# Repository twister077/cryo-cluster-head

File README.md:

# CryoClusterHead — Open-Source Cluster Headache Detection & Relief System

> **⚠ Experimental Research Project.** Not a certified medical product. Use at your own risk.

## Overview

Cluster headaches are among the most excruciatingly painful conditions known. This project explores an open-source hardware and software approach to **early detection of cluster headache flare-ups** using continuous skin temperature monitoring. 

By tracking rapid localized temperature changes ($\Delta T/\Delta t$) at the temple/neck area during the prodromal phase, our goal is to provide an early warning notification **minutes before peak pain hits**, allowing for timely intervention (such as cold therapy or medication).

---

## Current Focus & Development Tracks

The repository is structured into two main tracks:

### 🚀 Track A — Non-BLE Test Patch (Active Focus)
- **Hardware:** Miniature round PCB (`cryo-alert-patch/hardware/pcb/`) featuring **STM32L011** MCU + **TMP117** high-precision temperature sensor (B.Cu contact), CR1220 battery, piezo buzzer, LED, and tactile switch (`SW1`).
- **Firmware (`cryo-alert-patch/firmware-stm32/`)**: PlatformIO / STM32Cube HAL implementation featuring TMP117 I2C driver, ADC battery monitoring, alert state machine, and robust **$\Delta T/\Delta t$ flare-up detection** (validated with a host-side unit test suite).

### 📡 Track B — BLE & Companion Ecosystem (Planned / Later)
- **Hardware & Software:** nRF52832-based variants, `cryo-active-cooler/`, and `cryo-mobile-app/` (Flutter + Rust core).
- **Status:** Documented for future integration after Track A hardware testing and validation are completed.

---

## Community & Collaboration Welcome!

Building open-source medical/health hardware and embedded firmware is a massive undertaking for a single developer. **I cannot do this alone!** 

Whether you are an embedded firmware engineer, PCB designer (KiCad), mobile app developer, or a fellow cluster headache sufferer / researcher wanting to share insights — **your input, contributions, and feedback are immensely welcome.**

- **Open Issues & PRs:** Feel free to open issues or submit pull requests directly in this repository.
- **Discussions / Contact:** Reach out via GitHub issues or discussions to collaborate.

---

## Repository Structure

- `cryo-alert-patch/` — Hardware schematics, Gerber files, and firmware (`firmware-stm32/` for STM32 test track, `firmware-zephyr-ble/` for Zephyr/BLE).
- `cryo-mobile-app/` — Flutter companion app with Rust core for real-time $\Delta T/\Delta t$ analysis *(Track B)*.
- `cryo-active-cooler/` — Optional Peltier active cooling module concept *(Track B)*.
- `plan.md` — Detailed multi-phase project roadmap.

## License

- **Firmware:** MIT
- **Hardware:** CERN-OHL-S-2.0

---

## Contributors & AI Co-Developer

- **Twister077** — Project Initiator, Lead Concept & Hardware Architect.
- **Hermes Agent (Nous Research)** — AI Co-Developer & Engineering Assistant (assisted with KiCad schematic reconstruction, DRC/ERC validation, Gerber preparation, and STM32 PlatformIO firmware/testing).

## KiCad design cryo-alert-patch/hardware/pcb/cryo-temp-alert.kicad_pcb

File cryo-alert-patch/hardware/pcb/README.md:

# Cryo Temp Alert PCB — v6

**Date:** 2026-09-08
**Status:** Production-ready (0 real DRC errors, 32 cosmetic warnings; ERC 0 errors)
**Validation:** KiCad DRC/ERC + MCP SVG render + netlist cross-check

## Specs
- Board: Ø34mm round (radius 17mm)
- Layers: 2 (F.Cu + B.Cu)
- Components: 13 footprints
  - **U1** STM32L011 MCU (TSSOP-20) — F.Cu at (-3, 0)
  - **U2** TMP117 temperature sensor (TMP117xxDRV, WSON-6-1EP) — **B.Cu** at (0, 7) ← skin contact
  - **BT1** CR1220 battery holder — F.Cu
  - **BZ1** Piezo buzzer — F.Cu
  - **LED1** SMD LED — F.Cu
  - **SW1** SKQG tactile switch — F.Cu
  - **J1** Pin header 1x4 (POGO programmer) — F.Cu
  - **R1, R2** 4.7k I2C pull-ups — F.Cu
  - **R3** 10k (NRST pull-up), **R4** LED current limiter — F.Cu
  - **C1, C2** 100nF decoupling — B.Cu near MCU
- Nets: 12 (GND, VCC, SDA, SCL, NRST, VBAT_SENSE, BUZZER, LED_SIG, SW_SIG, I2C_ADDR, VDDA, DEC_100NF)

## Temperature sensor: TMP117 (deliberate choice)
The board uses the **TMP117** (by TI) as the skin temperature sensor, deliberately instead of the
MAX30208 — among other reasons, because of the simpler wiring in this phase.

- **Schematic symbol:** `Sensor_Temperature:TMP117xxDRV` (value `TMP117xxDRV`)
- **PCB footprint:** `WSON-6-1EP_2x2mm_P0.65mm_EP1x1.6mm` on B.Cu
- Same I2C pinout as the MAX30208 (SCL/SDA/ADD0/ALERT/V+/GND), so it can later be
  swapped for the MAX30208 in the Bluetooth revision.

> **Future:** the next revision will get Bluetooth (nRF) and the MAX30208 sensor.
> For now both the schematic and PCB are configured for the TMP117.

## Schematic (rebuilt 2026-09-08)
The schematic was fully rebuilt so it renders correctly in the KiCad GUI:
- **Real root UUID** (was all-null `00000000-...` → blank GUI sheet)
- **Real net labels** (46 total) connect the pins electrically
- **ERC: 0 errors** (7 cosmetic warnings: spare GPIOs on power rails + VBAT_SENSE test point)
- Components on an A4 sheet with net labels instead of only physical wires

## Contents of this bundle (v6)
- `cryo-temp-alert.kicad_sch` — schematic (rebuilt, renders correctly)
- `cryo-temp-alert.kicad_pcb` — PCB (U2 = TMP117)
- `cryo-temp-alert.kicad_pro` — project file
- `cryo-temp-alert.kicad_prl` — layout
- `sym-lib-table` / `fp-lib-table` — library configuration
- `schematic.pdf` — schematic export (rebuilt)
- `gerbers/cryo-temp-alert-jlcpcb.zip` — JLCPCB fabrication bundle (fresh export)
- `renders/cryo-3d-renders.zip` — 3D renders
- `cryo-temp-alert-drc.rpt` — KiCad DRC report (32 cosmetic warnings, 0 errors)
- `README.md` — this file

## For JLCPCB fabrication
Upload `gerbers/cryo-temp-alert-jlcpcb.zip` to https://jlcpcb.com/quote.
Contains 7 Gerber layers + drill + job file.

## For manual assembly
1. **U2 (TMP117)** on the **bottom** (B.Cu, skin-contact side)
2. Remaining components on top (F.Cu)
3. Insert CR1220 battery into BT1
4. Program via J1 POGO pads (SWDIO/SWDCLK/RESET/GND)

## Layers / design notes
- Sensor on B.Cu for skin-temperature measurement
- Pad-to-mask clearance 0.05mm (0.65mm pitch)
- Minimum track width 0.2mm

Validated: 0 real DRC errors, 0 ERC errors, 0 unconnected pads.

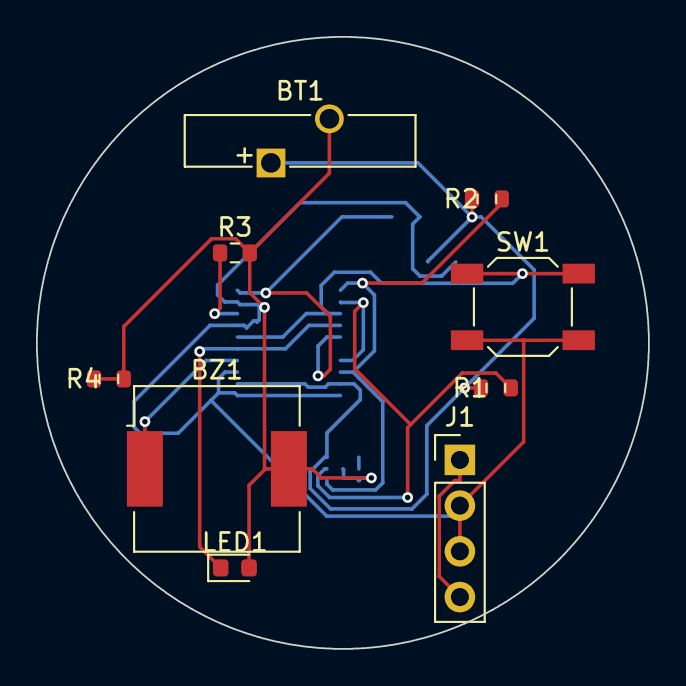
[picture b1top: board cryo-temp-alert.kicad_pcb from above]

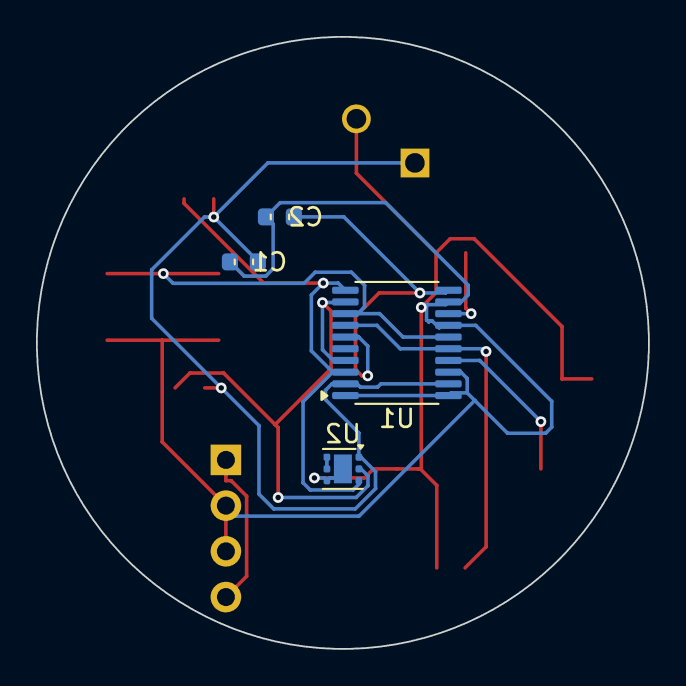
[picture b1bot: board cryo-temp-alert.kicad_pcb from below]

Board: 2 copper layers, 34.0 x 34.0 mm, 13 parts (4 on the bottom side), 11 nets.

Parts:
BT1: CR1220; Battery_Panasonic_CR1220-VCN_Vertical_CircularHoles
BZ1: Piezo; Buzzer_CUI_CPT-9019S-SMT
C1, C2: 100n; C_0603_1608Metric
J1: POGO-4; PinHeader_1x04_P2.54mm_Vertical
LED1: Groen; LED_0603_1608Metric
R1, R2: 4.7k; R_0603_1608Metric
R3: 10k; R_0603_1608Metric
R4: 2.2k; R_0603_1608Metric
SW1: Drukknop; SW_SPST_SKQG_WithoutStem
U1: STM32L011; TSSOP-20_4.4x6.5mm_P0.65mm
U2: TMP117xxDRV; WSON-6-1EP_2x2mm_P0.65mm_EP1x1.6mm

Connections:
BUZZER: BZ1.1, U1.7
GND: BT1.2, BZ1.2, C1.2, C2.2, J1.2, J1.3, LED1.2, R3.2, R4.1, R4.2, SW1.2, U1.2, U1.4, U1.8, U1.10, U1.11, U2.4, U2.7
I2C_ADDR: U2.5, U2.6
LED_SIG: LED1.1, U1.6, U1.17
NRST: R3.1, U1.3
SCL: R2.2, U1.13, U1.20, U2.3
SDA: R1.2, U1.14, U1.19, U2.2
SW_SIG: SW1.1, U1.5, U1.18
VBAT_SENSE: J1.1, J1.4
VCC: BT1.1, C1.1, R1.1, R2.1, U1.9, U1.12, U2.1
VDDA: C2.1, U1.1, U1.16

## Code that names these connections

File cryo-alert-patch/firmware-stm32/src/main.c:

#include "stm32l0xx_hal.h"
#include "tmp117.h"
#include "dTdt.h"
#include "power.h"

/* Pin mapping (matches KiCad v6 netlist) */
#define LED_PIN      GPIO_PIN_3   /* PB3 -> LED_SIG */
#define LED_PORT     GPIOB
#define BUZZER_PIN   GPIO_PIN_8   /* PA8 -> BUZZER */
#define BUZZER_PORT  GPIOA
#define BUTTON_PIN   GPIO_PIN_4   /* PB4 -> SW_SIG */
#define BUTTON_PORT  GPIOB
#define VBAT_PIN     GPIO_PIN_0   /* PA0 -> VBAT_SENSE (ADC) */
#define VBAT_PORT    GPIOA

/* Thresholds */
#define TEMP_HIGH_C   38.5f
#define TEMP_LOW_C    34.0f
#define TEMP_CRIT_HI  42.0f
#define TEMP_CRIT_LO  30.0f
#define VBAT_LOW      2.2f
#define DTDT_THRESHOLD 0.5f  /* °C/min rapid rise threshold for flare-up */

/* Timing (ms) */
#define MEASURE_PERIOD     2000
#define BLINK_NORMAL       2000
#define BLINK_WARNING      500
#define BLINK_ALERT        200
#define MUTE_DURATION      30000
#define DEBOUNCE           50

typedef enum {
    STATE_NORMAL = 0,
    STATE_WARNING,
    STATE_CRITICAL_ALERT,
    STATE_MUTED
} SystemState;

static SystemState state = STATE_NORMAL;
static uint32_t lastMeasure = 0;
static uint32_t lastBlink = 0;
static uint32_t muteStart = 0;
static uint8_t ledOn = 0;

static I2C_HandleTypeDef hi2c;
static ADC_HandleTypeDef hadc;
static TMP117_t sensor;
static dTdt_t dtdtTracker;

static void SystemClock_Config(void);
static void MX_GPIO_Init(void);
static void MX_I2C1_Init(void);
static void MX_ADC_Init(void);
static void Error_Handler(void);

int main(void) {
    HAL_Init();
    SystemClock_Config();
    MX_GPIO_Init();
    MX_I2C1_Init();
    MX_ADC_Init();
    Power_Init();
    dTdt_Init(&dtdtTracker);

    if (TMP117_Init(&sensor, &hi2c, TMP117_I2C_ADDR) != 0) {
        HAL_GPIO_WritePin(LED_PORT, LED_PIN, GPIO_PIN_SET);
    } else {
        TMP117_SetMode(&sensor, 0x00); /* continuous conversion */
    }

    while (1) {
        uint32_t now = HAL_GetTick();

        /* Button (mute/snooze) with debounce */
        if (HAL_GPIO_ReadPin(BUTTON_PORT, BUTTON_PIN) == GPIO_PIN_RESET) {
            HAL_Delay(DEBOUNCE);
            if (HAL_GPIO_ReadPin(BUTTON_PORT, BUTTON_PIN) == GPIO_PIN_RESET) {
                if (state == STATE_CRITICAL_ALERT || state == STATE_WARNING) {
                    state = STATE_MUTED;
                    muteStart = now;
                    HAL_GPIO_WritePin(BUZZER_PORT, BUZZER_PIN, GPIO_PIN_RESET);
                }
            }
        }

        if (state == STATE_MUTED && (now - muteStart) > MUTE_DURATION) {
            state = STATE_NORMAL;
        }

        /* Periodic measurement */
        if ((now - lastMeasure) >= MEASURE_PERIOD) {
            lastMeasure = now;

            float temp = 0;
            if (TMP117_ReadTempC(&sensor, &temp) != 0) {
                temp = 36.5f; /* fallback if read error */
            }

            /* Update dT/dt rate-of-change analysis */
            dTdt_Push(&dtdtTracker, temp);
            int flareUpDetected = dTdt_IsSpike(&dtdtTracker, DTDT_THRESHOLD);

            /* VBAT via ADC */
            HAL_ADC_Start(&hadc);
            HAL_ADC_PollForConversion(&hadc, 10);
            uint16_t adcRaw = HAL_ADC_GetValue(&hadc);
            HAL_ADC_Stop(&hadc);
            float vbat = (adcRaw * 3.0f / 4095.0f);

            if (state != STATE_MUTED) {
                if (temp < TEMP_CRIT_LO || temp > TEMP_CRIT_HI || vbat < VBAT_LOW || flareUpDetected) {
                    state = STATE_CRITICAL_ALERT;
                } else if (temp < TEMP_LOW_C || temp > TEMP_HIGH_C) {
                    state = STATE_WARNING;
                } else {
                    state = STATE_NORMAL;
                }
            }
        }

        /* Actuators */
        switch (state) {
            case STATE_NORMAL:
                if ((now - lastBlink) >= BLINK_NORMAL) {
                    lastBlink = now;
                    ledOn = !ledOn;
                    HAL_GPIO_WritePin(LED_PORT, LED_PIN, ledOn ? GPIO_PIN_SET : GPIO_PIN_RESET);
                }
                HAL_GPIO_WritePin(BUZZER_PORT, BUZZER_PIN, GPIO_PIN_RESET);
                break;

            case STATE_WARNING:
                if ((now - lastBlink) >= BLINK_WARNING) {
                    lastBlink = now;
                    ledOn = !ledOn;
                    HAL_GPIO_WritePin(LED_PORT, LED_PIN, ledOn ? GPIO_PIN_SET : GPIO_PIN_RESET);
                }
                HAL_GPIO_WritePin(BUZZER_PORT, BUZZER_PIN, GPIO_PIN_RESET);
                break;

            case STATE_CRITICAL_ALERT:
                if ((now - lastBlink) >= BLINK_ALERT) {
                    lastBlink = now;
                    ledOn = !ledOn;
                    HAL_GPIO_WritePin(LED_PORT, LED_PIN, ledOn ? GPIO_PIN_SET : GPIO_PIN_RESET);
                    HAL_GPIO_WritePin(BUZZER_PORT, BUZZER_PIN, ledOn ? GPIO_PIN_SET : GPIO_PIN_RESET);
                }
                break;

            case STATE_MUTED:
                HAL_GPIO_WritePin(LED_PORT, LED_PIN, GPIO_PIN_SET);
                HAL_GPIO_WritePin(BUZZER_PORT, BUZZER_PIN, GPIO_PIN_RESET);
                break;
        }

        /* Low-power sleep between iterations when not alarming */
        if (state == STATE_NORMAL) {
            Power_EnterSleepMode();
        }
    }
}

static void MX_I2C1_Init(void) {
    hi2c.Instance = I2C1;
    hi2c.Init.Timing = 0x2000090E; /* 100kHz */
    hi2c.Init.OwnAddress1 = 0;
    hi2c.Init.AddressingMode = I2C_ADDRESSINGMODE_7BIT;
    hi2c.Init.DualAddressMode = I2C_DUALADDRESS_DISABLE;
    hi2c.Init.GeneralCallMode = I2C_GENERALCALL_DISABLE;
    hi2c.Init.NoStretchMode = I2C_NOSTRETCH_DISABLE;
    if (HAL_I2C_Init(&hi2c) != HAL_OK) {
        Error_Handler();
    }
    if (HAL_I2CEx_ConfigAnalogFilter(&hi2c, I2C_ANALOGFILTER_ENABLE) != HAL_OK) {
        Error_Handler();
    }
    if (HAL_I2CEx_ConfigDigitalFilter(&hi2c, 0) != HAL_OK) {
        Error_Handler();
    }
}

static void MX_ADC_Init(void) {
    hadc.Instance = ADC1;
    hadc.Init.OversamplingMode = DISABLE;
    hadc.Init.ClockPrescaler = ADC_CLOCK_SYNC_PCLK_DIV4;
    hadc.Init.Resolution = ADC_RESOLUTION_12B;
    hadc.Init.DataAlign = ADC_DATAALIGN_RIGHT;
    hadc.Init.ScanConvMode = ADC_SCAN_DIRECTION_FORWARD;
    hadc.Init.EOCSelection = ADC_EOC_SINGLE_CONV;
    hadc.Init.LowPowerAutoWait = DISABLE;
    hadc.Init.LowPowerAutoPowerOff = DISABLE;
    hadc.Init.ContinuousConvMode = DISABLE;
    hadc.Init.DiscontinuousConvMode = DISABLE;
    hadc.Init.ExternalTrigConv = ADC_SOFTWARE_START;
    hadc.Init.SamplingTime = ADC_SAMPLETIME_7CYCLES_5;
    if (HAL_ADC_Init(&hadc) != HAL_OK) {
        Error_Handler();
    }
    ADC_ChannelConfTypeDef sConfig = {0};
    sConfig.Channel = ADC_CHANNEL_0; /* PA0 */
    sConfig.Rank = ADC_RANK_CHANNEL_NUMBER;
    if (HAL_ADC_ConfigChannel(&hadc, &sConfig) != HAL_OK) {
        Error_Handler();
    }
}

static void MX_GPIO_Init(void) {
    GPIO_InitTypeDef GPIO_InitStruct = {0};

    __HAL_RCC_GPIOA_CLK_ENABLE();
    __HAL_RCC_GPIOB_CLK_ENABLE();

    /* LED (PB3) output */
    HAL_GPIO_WritePin(GPIOB, GPIO_PIN_3, GPIO_PIN_RESET);
    GPIO_InitStruct.Pin = GPIO_PIN_3;
    GPIO_InitStruct.Mode = GPIO_MODE_OUTPUT_PP;
    GPIO_InitStruct.Pull = GPIO_NOPULL;
    GPIO_InitStruct.Speed = GPIO_SPEED_FREQ_LOW;
    HAL_GPIO_Init(GPIOB, &GPIO_InitStruct);

    /* Buzzer (PA8) output */
    HAL_GPIO_WritePin(GPIOA, GPIO_PIN_8, GPIO_PIN_RESET);
    GPIO_InitStruct.Pin = GPIO_PIN_8;
    HAL_GPIO_Init(GPIOA, &GPIO_InitStruct);

    /* Button (PB4) input pull-up */
    GPIO_InitStruct.Pin = GPIO_PIN_4;
    GPIO_InitStruct.Mode = GPIO_MODE_INPUT;
    GPIO_InitStruct.Pull = GPIO_PULLUP;
    HAL_GPIO_Init(GPIOB, &GPIO_InitStruct);

    /* VBAT sense (PA0) analog */
    GPIO_InitStruct.Pin = GPIO_PIN_0;
    GPIO_InitStruct.Mode = GPIO_MODE_ANALOG;
    GPIO_InitStruct.Pull = GPIO_NOPULL;
    HAL_GPIO_Init(GPIOA, &GPIO_InitStruct);
}

static void SystemClock_Config(void) {
    RCC_OscInitTypeDef RCC_OscInitStruct = {0};
    RCC_ClkInitTypeDef RCC_ClkInitStruct = {0};

    RCC_OscInitStruct.OscillatorType = RCC_OSCILLATORTYPE_HSI;
    RCC_OscInitStruct.HSIState = RCC_HSI_ON;
    RCC_OscInitStruct.HSICalibrationValue = RCC_HSICALIBRATION_DEFAULT;
    RCC_OscInitStruct.PLL.PLLState = RCC_PLL_NONE;
    if (HAL_RCC_OscConfig(&RCC_OscInitStruct) != HAL_OK) {
        Error_Handler();
    }

    RCC_ClkInitStruct.ClockType = RCC_CLOCKTYPE_HCLK | RCC_CLOCKTYPE_SYSCLK | RCC_CLOCKTYPE_PCLK1;
    RCC_ClkInitStruct.SYSCLKSource = RCC_SYSCLKSOURCE_HSI;
    RCC_ClkInitStruct.AHBCLKDivider = RCC_SYSCLK_DIV1;
    RCC_ClkInitStruct.APB1CLKDivider = RCC_HCLK_DIV1;
    if (HAL_RCC_ClockConfig(&RCC_ClkInitStruct, FLASH_LATENCY_0) != HAL_OK) {
        Error_Handler();
    }
}

static void Error_Handler(void) {
    __disable_irq();
    while (1) {
    }
}
